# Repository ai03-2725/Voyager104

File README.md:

# Voyager104
A full-size PCB for the Voyager family

#### In light of recent claims that I am 100% liable for any of my open source PCBs, I am adding this disclaimer.
#### I provide these PCBs as a reference for designing keyboard PCBs. Using them within your projects will require a will to do research of one's own and to learn the workings of them, potentially fixing issues if they exist.
# I provide these PCBs without liability and without any guarantees regarding functionality, as expressed in the MIT license under which all of these PCBs are licensed.

### Features
* In-switch LED backlighting
* Dual flex slot cutout for typing comfort
* Decent amount of layout compatibility
* Over-current and static discharge protection
* Fully open-source

### The Voyager PCB Family
The Voyager PCBs offer fully featured PCBs fit for any keyboard, whether mass production or high-end.

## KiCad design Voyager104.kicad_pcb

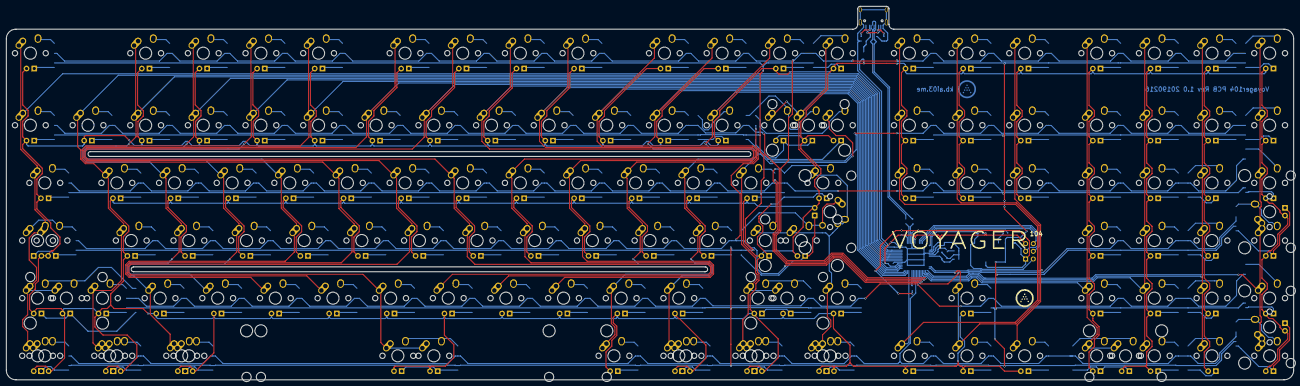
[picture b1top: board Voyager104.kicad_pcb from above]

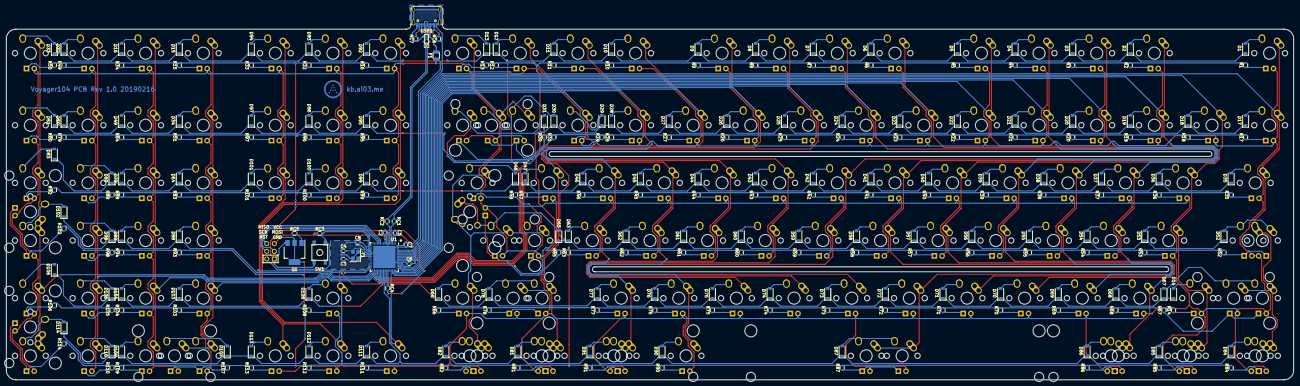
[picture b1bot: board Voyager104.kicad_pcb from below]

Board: 2 copper layers, 425.4 x 123.4 mm, 380 parts (250 on the bottom side), 275 nets.

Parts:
C2, C5: 1uF; C_0603
C3, C4: 22pF; C_0603
C6, C7, C8: 0.1uF; C_0603
D1, D2, D3, D4, D5, D6, D7, D8, D9, D10, D11, D12, D13, D14, D15, D16, D17, D18, D19, D20, D21, D22, D23, D24, D25, D26, D27, D28, D29, D30, D31, D32, D33, D34, D35, D36, D37, D38, D39, D40, D41, D42, D43, D44, D45, D46, D47, D48, D49, D50, D51, D52, D53, D54, D55, D56, D57, D58, D59, D60, D61, D62, D63, D64, D65, D66, D67, D68, D69, D70, D71, D72, D73, D74, D75, D76, D77, D78, D79, D80, D81, D82, D83, D84, D85, D86, D87, D88, D89, D90, D91, D92, D93, D94, D95, D96, D97, D98, D99, D100, D101, D102, D103, D104, D105, D106, D107, D108, D109, D110, D111, D112, D113, D114: SOD-323; D_SOD-123
F1: 500mA; Fuse_SMD1206_Reflow
J1: AVR-ISP-6; Reset_Pretty-Mask
MX_#0_1, MX_#1, MX_#2, MX_#3, MX_#4, MX_#5, MX_#6, MX_#7, MX_#8, MX_#9: MX-1U
MX_'1: MX-1U
MX_,1: MX-1U
MX_-1: MX-1U
MX_.1: MX-1U
MX_/1: MX-1U
MX_;1: MX-1U
MX_=1: MX-1U
MX_A1: MX-1U
MX_B1: MX-1U
MX_BACK1: MX-2U
MX_BACK2, MX_BACK3: MX-1U
MX_C1: MX-1U
MX_CLOCK1: MX-1.75U
MX_CLOCK2: MX-1.25U; MX-1.25U-FLIPPED
MX_D1: MX-1U
MX_DEL1: MX-1U
MX_DN1: MX-1U
MX_E1: MX-1U
MX_END1: MX-1U
MX_ESC1: MX-1U
MX_F1: MX-1U
MX_FN1, MX_FN2, MX_FN3, MX_FN4, MX_FN5, MX_FN6, MX_FN7, MX_FN8, MX_FN9, MX_FN10, MX_FN11, MX_FN12: MX-1U
MX_G1: MX-1U
MX_H1: MX-1U
MX_HOME1: MX-1U
MX_I1: MX-1U
MX_INS1: MX-1U
MX_J1: MX-1U
MX_K1: MX-1U
MX_L1: MX-1U
MX_LALT1: MX-1.25U
MX_LALT2: MX-1.5U; MX-1.5U-FLIPPED
MX_LCTRL1: MX-1.25U
MX_LCTRL2: MX-1.5U; MX-1.5U-FLIPPED
MX_LFT1: MX-1U
MX_LGUI1: MX-1.25U
MX_LGUI2: MX-1U; MX-1U-FLIPPED
MX_LSHIFT1: MX-2.25U
MX_LSHIFT2: MX-1.25U
MX_LSHIFT3: MX-1U
MX_M1: MX-1U
MX_N1: MX-1U
MX_NUM1, MX_NUM2, MX_NUM3, MX_NUM4, MX_NUM5, MX_NUM6, MX_NUM7, MX_NUM8, MX_NUM9, MX_NUM10, MX_NUM11, MX_NUM12, MX_NUM13, MX_NUM14, MX_NUM15, MX_NUM16, MX_NUM17, MX_NUM18, MX_NUM19, MX_NUM20, MX_NUM21, MX_NUM22, MX_NUM23, MX_NUM24: MX-1U
MX_NUM_EX1, MX_NUM_EX2, MX_NUM_EX3: MX-2U; MX-2U-ReversedStabilizers
MX_O1: MX-1U
MX_P1: MX-1U
MX_PAUSE1: MX-1U
MX_PGDN1: MX-1U
MX_PGUP1: MX-1U
MX_PRINT1: MX-1U
MX_Q1: MX-1U
MX_R1: MX-1U
MX_RALT1: MX-1.25U
MX_RALT2: MX-1.5U
MX_RCTRL1: MX-1.25U; MX-1.25U-FLIPPED
MX_RCTRL2: MX-1.5U
MX_RETURN1: MX-2.25U
MX_RETURN2: MX-ISO; MX-ISO-ReversedStabilizers
MX_RGUI1: MX-1.25U; MX-1.25U-FLIPPED
MX_RGUI2: MX-1U
MX_RMENU1: MX-1.25U; MX-1.25U-FLIPPED
MX_RSHIFT1: MX-2.75U
MX_RSHIFT2: MX-1.75U
MX_RSHIFT3: MX-1U
MX_RT1: MX-1U
MX_S1: MX-1U
MX_SLOCK1: MX-1U
MX_SP1: MX-6.25U; MX-6.25U-ReversedStabilizers
MX_SP2: MX-7U; MX-7U-ReversedStabilizers
MX_T1: MX-1U
MX_TAB1: MX-1.5U
MX_U1: MX-1U
MX_UP1: MX-1U
MX_V1: MX-1U
MX_W1: MX-1U
MX_X1: MX-1U
MX_Y1: MX-1U
MX_Z1: MX-1U
MX_[1: MX-1U
MX_\1: MX-1.5U
MX_\2: MX-1U
MX_]1: MX-1U
MX_`1: MX-1U
Q1: DSS60601MZ4-13; SOT-223-3_TabPin2
R1, R2, R3, R4, R5, R6, R7, R8, R9, R10, R11, R12, R13, R14, R15, R16, R17, R18, R19, R20, R21, R22, R23, R24, R25, R26, R27, R28, R29, R30, R31, R32, R33, R34, R35, R36, R37, R38, R39, R40, R41, R42, R43, R44, R45, R46, R47, R48, R49, R50, R51, R52, R53, R54, R55, R56, R57, R58, R59, R60, R61, R62, R63, R64, R65, R66, R67, R68, R69, R70, R71, R72, R73, R74, R75, R76, R77, R78, R79, R80, R81, R82, R83, R84, R85, R86, R87, R88, R89, R90, R91, R92, R93, R94, R95, R96, R97, R98, R99, R100, R101, R102, R103, R104, R105, R106, R107, R108, R109, R110, R111, R112, R113, R114: 1k; R_0603
RC1, RC2: 22; R_0603
RC3: 10k; R_0603
RC4: 1k; R_0603
RC5: 1.5k; R_0603
RC6, RC7: 5k1; R_0603
SW1: SW_Push; SKQG-1155865
U1: AT90USB1286-AU; QFN-64-1EP_9x9mm_Pitch0.5mm
U2: PRTR5V0U2X; SOT143B
USB1: HRO-TYPE-C-31-M-12; HRO-TYPE-C-31-M-12-Assembly
Y1: 16MHz; Crystal_SMD_3225-4pin_3.2x2.5mm

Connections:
+5V: C5.2, C6.2, C7.2, C8.2, F1.1, J1.2, MX_#0_1.3, MX_#1.3, MX_#2.3, MX_#3.3, MX_#4.3, MX_#5.3, MX_#6.3, MX_#7.3, MX_#8.3, MX_#9.3, MX_'1.3, MX_,1.3, MX_-1.3, MX_.1.3, MX_/1.3, MX_;1.3, MX_=1.3, MX_A1.3, MX_B1.3, MX_BACK1.3, MX_BACK2.3, MX_BACK3.3, MX_C1.3, MX_CLOCK1.3, MX_CLOCK2.3, MX_D1.3, MX_DEL1.3, MX_DN1.3, MX_E1.3, MX_END1.3, MX_ESC1.3, MX_F1.3, MX_FN1.3, MX_FN2.3, MX_FN3.3, MX_FN4.3, MX_FN5.3, MX_FN6.3, MX_FN7.3, MX_FN8.3, MX_FN9.3, MX_FN10.3, MX_FN11.3, MX_FN12.3, MX_G1.3, MX_H1.3, MX_HOME1.3, MX_I1.3, MX_INS1.3, MX_J1.3, MX_K1.3, MX_L1.3, MX_LALT1.3, MX_LALT2.3, MX_LCTRL1.3, MX_LCTRL2.3, MX_LFT1.3, MX_LGUI1.3, MX_LGUI2.3, MX_LSHIFT1.3, MX_LSHIFT2.3, MX_LSHIFT3.3, MX_M1.3, MX_N1.3, MX_NUM1.3, MX_NUM2.3, MX_NUM3.3, MX_NUM4.3, MX_NUM5.3, MX_NUM6.3, MX_NUM7.3, MX_NUM8.3, MX_NUM9.3, MX_NUM10.3, MX_NUM11.3, MX_NUM12.3, MX_NUM13.3, MX_NUM14.3, MX_NUM15.3, MX_NUM16.3, MX_NUM17.3, MX_NUM18.3, MX_NUM19.3, MX_NUM20.3, MX_NUM21.3, MX_NUM22.3, MX_NUM23.3, MX_NUM24.3, MX_NUM_EX1.3, MX_NUM_EX2.3, MX_NUM_EX3.3, MX_O1.3, MX_P1.3, MX_PAUSE1.3, MX_PGDN1.3, MX_PGUP1.3, MX_PRINT1.3, MX_Q1.3, MX_R1.3, MX_RALT1.3, MX_RALT2.3, MX_RCTRL1.3, MX_RCTRL2.3, MX_RETURN1.3, MX_RETURN2.3, MX_RGUI1.3, MX_RGUI2.3, MX_RMENU1.3, MX_RSHIFT1.3, MX_RSHIFT2.3, MX_RSHIFT3.3, MX_RT1.3, MX_S1.3, MX_SLOCK1.3, MX_SP1.3, MX_SP2.3, MX_T1.3, MX_TAB1.3, MX_U1.3, MX_UP1.3, MX_V1.3, MX_W1.3, MX_X1.3, MX_Y1.3, MX_Z1.3, MX_[1.3, MX_\1.3, MX_\2.3, MX_]1.3, MX_`1.3, RC3.1, U1.3, U1.8, U1.21, U1.52, U1.64
COL0: MX_CLOCK1.1, MX_CLOCK2.2, MX_ESC1.1, MX_LCTRL1.1, MX_LCTRL2.1, MX_LSHIFT1.1, MX_LSHIFT2.1, MX_TAB1.1, MX_`1.1, U1.61
COL1: MX_#1.1, MX_A1.1, MX_LGUI1.1, MX_LGUI2.1, MX_LSHIFT3.1, MX_Q1.1, U1.60
COL2: MX_#2.1, MX_FN1.1, MX_LALT1.1, MX_LALT2.1, MX_S1.1, MX_W1.1, MX_Z1.1, U1.59
COL3: MX_#3.1, MX_D1.1, MX_E1.1, MX_FN2.1, MX_X1.1, U1.58
COL4: MX_#4.1, MX_C1.1, MX_F1.1, MX_FN3.1, MX_R1.1, U1.57
COL5: MX_#5.1, MX_FN4.1, MX_G1.1, MX_T1.1, MX_V1.1, U1.56
COL6: MX_#6.1, MX_B1.1, MX_FN5.1, MX_H1.1, MX_SP1.1, MX_SP2.1, MX_Y1.1, U1.55
COL7: MX_#7.1, MX_FN6.1, MX_J1.1, MX_N1.1, MX_U1.1, U1.54
COL8: MX_#8.1, MX_FN7.1, MX_I1.1, MX_K1.1, MX_M1.1, U1.51
COL9: MX_#9.1, MX_,1.1, MX_FN8.1, MX_L1.1, MX_O1.1, U1.50
COL10: MX_#0_1.1, MX_.1.1, MX_;1.1, MX_FN9.1, MX_P1.1, MX_RALT1.1, U1.49
COL11: MX_'1.1, MX_-1.1, MX_/1.1, MX_FN10.1, MX_RALT2.1, MX_RGUI1.1, MX_[1.1, U1.48
COL12: MX_=1.1, MX_BACK3.1, MX_FN11.1, MX_RGUI2.1, MX_RMENU1.1, MX_RSHIFT1.1, MX_RSHIFT2.1, MX_]1.1, U1.47
COL13: MX_BACK1.1, MX_BACK2.1, MX_FN12.1, MX_RCTRL1.1, MX_RCTRL2.1, MX_RETURN1.1, MX_RETURN2.1, MX_RSHIFT3.1, MX_\1.1, MX_\2.1, U1.46
COL14: MX_DEL1.1, MX_INS1.1, MX_LFT1.1, MX_PRINT1.1, U1.45
COL15: MX_DN1.1, MX_END1.1, MX_HOME1.1, MX_SLOCK1.1, MX_UP1.1, U1.32
COL16: MX_PAUSE1.1, MX_PGDN1.1, MX_PGUP1.1, MX_RT1.1, U1.31
COL17: MX_NUM1.1, MX_NUM5.1, MX_NUM9.1, MX_NUM13.1, MX_NUM17.1, MX_NUM21.1, MX_NUM_EX3.1, U1.36
COL18: MX_NUM2.1, MX_NUM6.1, MX_NUM10.1, MX_NUM14.1, MX_NUM18.1, MX_NUM22.1, U1.35
COL19: MX_NUM3.1, MX_NUM7.1, MX_NUM11.1, MX_NUM15.1, MX_NUM19.1, MX_NUM23.1, U1.34
COL20: MX_NUM4.1, MX_NUM8.1, MX_NUM12.1, MX_NUM16.1, MX_NUM20.1, MX_NUM24.1, MX_NUM_EX1.1, MX_NUM_EX2.1, U1.33
D+: RC2.2, U1.5
D-: RC1.1, U1.4
GND: C2.2, C3.2, C4.2, C5.1, C6.1, C7.1, C8.1, J1.6, Q1.3, RC4.2, RC6.1, RC7.1, SW1.1, U1.6, U1.22, U1.53, U1.63, U1.65, U2.1, USB1.1, USB1.12, USB1.13, Y1.2, Y1.4
LEDGND: Q1.2, R1.2, R2.2, R3.2, R4.2, R5.2, R6.2, R7.2, R8.2, R9.2, R10.2, R11.2, R12.2, R13.2, R14.2, R15.2, R16.2, R17.2, R18.2, R19.2, R20.2, R21.2, R22.2, R23.2, R24.2, R25.2, R26.2, R27.2, R28.2, R29.2, R30.2, R31.2, R32.2, R33.2, R34.2, R35.2, R36.2, R37.2, R38.2, R39.2, R40.2, R41.2, R42.2, R43.2, R44.2, R45.2, R46.2, R47.2, R48.2, R49.2, R50.2, R51.2, R52.2, R53.2, R54.2, R55.2, R56.2, R57.2, R58.2, R59.2, R60.2, R61.2, R62.2, R63.2, R64.2, R65.2, R66.2, R67.2, R68.2, R69.2, R70.2, R71.2, R72.2, R73.2, R74.2, R75.2, R76.2, R77.2, R78.2, R79.2, R80.2, R81.2, R82.2, R83.2, R84.2, R85.2, R86.2, R87.2, R88.2, R89.2, R90.2, R91.2, R92.2, R93.2, R94.2, R95.2, R96.2, R97.2, R98.2, R99.2, R100.2, R101.2, R102.2, R103.2, R104.2, R105.2, R106.2, R107.2, R108.2, R109.2, R110.2, R111.2, R112.2, R113.2, R114.2
MISO: J1.1, U1.13
MOSI: J1.4, U1.12
unnamed: C2.1, U1.7
unnamed: D1.2, MX_ESC1.2
unnamed: D2.2, MX_FN1.2
unnamed: D3.2, MX_FN2.2
unnamed: D4.2, MX_FN3.2
unnamed: D5.2, MX_FN4.2
unnamed: D6.2, MX_FN5.2
unnamed: D7.2, MX_FN6.2
unnamed: D8.2, MX_FN7.2
unnamed: D9.2, MX_FN8.2
unnamed: D10.2, MX_FN9.2
unnamed: D11.2, MX_FN10.2
unnamed: D12.2, MX_FN11.2
unnamed: D13.2, MX_FN12.2
unnamed: D14.2, MX_LSHIFT3.2
unnamed: D15.2, MX_NUM1.2
unnamed: D16.2, MX_NUM2.2
unnamed: D17.2, MX_`1.2
unnamed: D18.2, MX_#1.2
unnamed: D19.2, MX_#2.2
unnamed: D20.2, MX_#3.2
unnamed: D21.2, MX_#4.2
unnamed: D22.2, MX_#5.2
unnamed: D23.2, MX_#6.2
unnamed: D24.2, MX_#7.2
unnamed: D25.2, MX_#8.2
unnamed: D26.2, MX_#9.2
unnamed: D27.2, MX_#0_1.2
unnamed: D28.2, MX_-1.2
unnamed: D29.2, MX_=1.2
unnamed: D30.2, MX_BACK1.2, MX_BACK2.2
unnamed: D31.2, MX_BACK3.2
unnamed: D32.2, MX_NUM3.2
unnamed: D33.2, MX_NUM4.2
unnamed: D34.2, MX_NUM5.2
unnamed: D35.2, MX_TAB1.2
unnamed: D36.2, MX_Q1.2
unnamed: D37.2, MX_W1.2
unnamed: D38.2, MX_E1.2
unnamed: D39.2, MX_R1.2
unnamed: D40.2, MX_T1.2
unnamed: D41.2, MX_Y1.2
unnamed: D42.2, MX_U1.2
unnamed: D43.2, MX_I1.2
unnamed: D44.2, MX_O1.2
unnamed: D45.2, MX_P1.2
unnamed: D46.2, MX_[1.2
unnamed: D47.2, MX_]1.2
unnamed: D48.2, MX_\1.2, MX_\2.2
unnamed: D49.2, MX_NUM6.2
unnamed: D50.2, MX_NUM7.2
unnamed: D51.2, MX_NUM8.2
unnamed: D52.2, MX_CLOCK1.2, MX_CLOCK2.1
unnamed: D53.2, MX_A1.2
unnamed: D54.2, MX_S1.2
unnamed: D55.2, MX_D1.2
unnamed: D56.2, MX_F1.2
unnamed: D57.2, MX_G1.2
unnamed: D58.2, MX_H1.2
unnamed: D59.2, MX_J1.2
unnamed: D60.2, MX_K1.2
unnamed: D61.2, MX_L1.2
unnamed: D62.2, MX_;1.2
unnamed: D63.2, MX_'1.2
unnamed: D64.2, MX_NUM9.2
unnamed: D65.2, MX_RETURN1.2, MX_RETURN2.2
unnamed: D66.2, MX_RSHIFT3.2
unnamed: D67.2, MX_LSHIFT1.2, MX_LSHIFT2.2
unnamed: D68.2, MX_Z1.2
unnamed: D69.2, MX_X1.2
unnamed: D70.2, MX_C1.2
unnamed: D71.2, MX_V1.2
unnamed: D72.2, MX_B1.2
unnamed: D73.2, MX_N1.2
unnamed: D74.2, MX_M1.2
unnamed: D75.2, MX_,1.2
unnamed: D76.2, MX_.1.2
unnamed: D77.2, MX_/1.2
unnamed: D78.2, MX_RSHIFT1.2, MX_RSHIFT2.2
unnamed: D79.2, MX_NUM10.2
unnamed: D80.2, MX_NUM11.2
unnamed: D81.2, MX_RGUI2.2, MX_RMENU1.2
unnamed: D82.2, MX_RCTRL1.2, MX_RCTRL2.2
unnamed: D83.2, MX_NUM12.2
unnamed: D84.2, MX_LCTRL1.2, MX_LCTRL2.2
unnamed: D85.2, MX_LGUI1.2, MX_LGUI2.2
unnamed: D86.2, MX_LALT1.2, MX_LALT2.2
unnamed: D87.2, MX_SP1.2, MX_SP2.2
unnamed: D88.2, MX_NUM13.2
unnamed: D89.2, MX_NUM14.2
unnamed: D90.2, MX_RALT1.2
unnamed: D91.2, MX_RALT2.2, MX_RGUI1.2
unnamed: D92.2, MX_PRINT1.2
unnamed: D93.2, MX_SLOCK1.2
unnamed: D94.2, MX_PAUSE1.2
unnamed: D95.2, MX_INS1.2
unnamed: D96.2, MX_HOME1.2
unnamed: D97.2, MX_PGUP1.2
unnamed: D98.2, MX_NUM15.2
unnamed: D99.2, MX_DEL1.2
unnamed: D100.2, MX_END1.2
unnamed: D101.2, MX_PGDN1.2
unnamed: D102.2, MX_NUM16.2, MX_NUM_EX1.2
unnamed: D103.2, MX_NUM17.2
unnamed: D104.2, MX_NUM18.2
unnamed: D105.2, MX_NUM19.2
unnamed: D106.2, MX_NUM20.2
unnamed: D107.2, MX_NUM21.2, MX_NUM_EX3.2
unnamed: D108.2, MX_UP1.2
unnamed: D109.2, MX_NUM22.2
unnamed: D110.2, MX_NUM23.2
unnamed: D111.2, MX_LFT1.2
unnamed: D112.2, MX_DN1.2
unnamed: D113.2, MX_RT1.2
unnamed: D114.2, MX_NUM24.2, MX_NUM_EX2.2
unnamed: MX_#0_1.4, R27.1
unnamed: MX_#1.4, R18.1
unnamed: MX_#2.4, R19.1
unnamed: MX_#3.4, R20.1
unnamed: MX_#4.4, R21.1
unnamed: MX_#5.4, R22.1
unnamed: MX_#6.4, R23.1
unnamed: MX_#7.4, R24.1
unnamed: MX_#8.4, R25.1
unnamed: MX_#9.4, R26.1
unnamed: MX_'1.4, R63.1
unnamed: MX_,1.4, R75.1
unnamed: MX_-1.4, R28.1
unnamed: MX_.1.4, R76.1
unnamed: MX_/1.4, R77.1
unnamed: MX_;1.4, R62.1
unnamed: MX_=1.4, R29.1
unnamed: MX_A1.4, R53.1
unnamed: MX_B1.4, R72.1
unnamed: MX_BACK1.4, MX_BACK2.4, R30.1
unnamed: MX_BACK3.4, R31.1
unnamed: MX_C1.4, R70.1
unnamed: MX_CLOCK1.4, MX_CLOCK2.4, R52.1
unnamed: MX_D1.4, R55.1
unnamed: MX_DEL1.4, R99.1
unnamed: MX_DN1.4, R112.1
unnamed: MX_E1.4, R38.1
unnamed: MX_END1.4, R100.1
unnamed: MX_ESC1.4, R1.1
unnamed: MX_F1.4, R56.1
unnamed: MX_FN1.4, R2.1
unnamed: MX_FN2.4, R3.1
unnamed: MX_FN3.4, R4.1
unnamed: MX_FN4.4, R5.1
unnamed: MX_FN5.4, R6.1
unnamed: MX_FN6.4, R7.1
unnamed: MX_FN7.4, R8.1
unnamed: MX_FN8.4, R9.1
unnamed: MX_FN9.4, R10.1
unnamed: MX_FN10.4, R11.1
unnamed: MX_FN11.4, R12.1
unnamed: MX_FN12.4, R13.1
unnamed: MX_G1.4, R57.1
unnamed: MX_H1.4, R58.1
unnamed: MX_HOME1.4, R96.1
unnamed: MX_I1.4, R43.1
unnamed: MX_INS1.4, R95.1
unnamed: MX_J1.4, R59.1
unnamed: MX_K1.4, R60.1
unnamed: MX_L1.4, R61.1
unnamed: MX_LALT1.4, MX_LALT2.4, R86.1
unnamed: MX_LCTRL1.4, MX_LCTRL2.4, R84.1
unnamed: MX_LFT1.4, R111.1
unnamed: MX_LGUI1.4, MX_LGUI2.4, R85.1
unnamed: MX_LSHIFT1.4, MX_LSHIFT2.4, R67.1
unnamed: MX_LSHIFT3.4, R14.1
unnamed: MX_M1.4, R74.1
unnamed: MX_N1.4, R73.1
unnamed: MX_NUM1.4, R15.1
unnamed: MX_NUM2.4, R34.1
unnamed: MX_NUM3.4, R49.1
unnamed: MX_NUM4.4, R50.1
unnamed: MX_NUM5.4, R51.1
unnamed: MX_NUM6.4, R64.1
unnamed: MX_NUM7.4, R79.1
unnamed: MX_NUM8.4, R80.1
unnamed: MX_NUM9.4, R83.1
unnamed: MX_NUM10.4, R88.1
unnamed: MX_NUM11.4, R89.1
unnamed: MX_NUM12.4, R92.1
unnamed: MX_NUM13.4, R93.1
unnamed: MX_NUM14.4, R94.1
unnamed: MX_NUM15.4, R98.1
unnamed: MX_NUM16.4, MX_NUM_EX1.4, R102.1
unnamed: MX_NUM17.4, R103.1
unnamed: MX_NUM18.4, R104.1
unnamed: MX_NUM19.4, R105.1
unnamed: MX_NUM20.4, R106.1
unnamed: MX_NUM21.4, MX_NUM_EX3.4, R107.1
unnamed: MX_NUM22.4, R109.1
unnamed: MX_NUM23.4, R110.1
unnamed: MX_NUM24.4, MX_NUM_EX2.4, R114.1
unnamed: MX_O1.4, R44.1
unnamed: MX_P1.4, R45.1
unnamed: MX_PAUSE1.4, R33.1
unnamed: MX_PGDN1.4, R101.1
unnamed: MX_PGUP1.4, R97.1
unnamed: MX_PRINT1.4, R16.1
unnamed: MX_Q1.4, R36.1
unnamed: MX_R1.4, R39.1
unnamed: MX_RALT1.4, R90.1
unnamed: MX_RALT2.4, MX_RGUI1.4, R91.1
unnamed: MX_RCTRL1.4, MX_RCTRL2.4, R82.1
unnamed: MX_RETURN1.4, MX_RETURN2.4, R65.1
unnamed: MX_RGUI2.4, MX_RMENU1.4, R81.1
unnamed: MX_RSHIFT1.4, MX_RSHIFT2.4, R78.1
unnamed: MX_RSHIFT3.4, R66.1
unnamed: MX_RT1.4, R113.1
unnamed: MX_S1.4, R54.1
unnamed: MX_SLOCK1.4, R32.1
unnamed: MX_SP1.4, MX_SP2.4, R87.1
unnamed: MX_T1.4, R40.1
unnamed: MX_TAB1.4, R35.1
unnamed: MX_U1.4, R42.1
unnamed: MX_UP1.4, R108.1
unnamed: MX_V1.4, R71.1
unnamed: MX_W1.4, R37.1
unnamed: MX_X1.4, R69.1
unnamed: MX_Y1.4, R41.1
unnamed: MX_Z1.4, R68.1
unnamed: MX_[1.4, R46.1
unnamed: MX_\1.4, MX_\2.4, R48.1
unnamed: MX_]1.4, R47.1
unnamed: MX_`1.4, R17.1
unnamed: Q1.1, RC5.2
unnamed: RC1.2, U2.3, USB1.5, USB1.7
unnamed: RC2.1, U2.2, USB1.6, USB1.8
unnamed: RC4.1, U1.43
unnamed: RC5.1, U1.17
unnamed: RC6.2, USB1.4
unnamed: RC7.2, USB1.10
RESET: J1.5, RC3.2, SW1.2, U1.20
ROW0: D1.1, D2.1, D3.1, D4.1, D5.1, D6.1, D7.1, D8.1, D9.1, D10.1, D11.1, D12.1, D13.1, D15.1, D16.1, D32.1, D33.1, D92.1, D93.1, D94.1, U1.37
ROW1: D17.1, D18.1, D19.1, D20.1, D21.1, D22.1, D23.1, D24.1, D25.1, D26.1, D27.1, D28.1, D29.1, D30.1, D34.1, D49.1, D50.1, D51.1, D95.1, D96.1, D97.1, U1.38
ROW2: D35.1, D36.1, D37.1, D38.1, D39.1, D40.1, D41.1, D42.1, D43.1, D44.1, D45.1, D46.1, D47.1, D48.1, D64.1, D79.1, D80.1, D83.1, D99.1, D100.1, D101.1, U1.39
ROW3: D31.1, D52.1, D53.1, D54.1, D55.1, D56.1, D57.1, D58.1, D59.1, D60.1, D61.1, D62.1, D63.1, D65.1, D88.1, D89.1, D98.1, D102.1, U1.40
ROW4: D14.1, D66.1, D67.1, D68.1, D69.1, D70.1, D71.1, D72.1, D73.1, D74.1, D75.1, D76.1, D77.1, D78.1, D103.1, D104.1, D105.1, D106.1, D108.1, U1.41
ROW5: D81.1, D82.1, D84.1, D85.1, D86.1, D87.1, D90.1, D91.1, D107.1, D109.1, D110.1, D111.1, D112.1, D113.1, D114.1, U1.42
SCK: J1.3, U1.11
VCC: F1.2, U2.4, USB1.2, USB1.11
XTAL1: C3.1, U1.24, Y1.1
XTAL2: C4.1, U1.23, Y1.3

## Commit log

2019-02-17 Paste in Voyager87 files
2019-02-17 Add submodules
2019-02-17 Build PCB
